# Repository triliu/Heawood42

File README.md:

# Heawood42

The Heawood42 is a diodeless 42-key ortho-linear split keyboard that uses any pro micro microcontroller. The Heawood42 utilises a new type of circuit design stemming from graph theory and mathematical design theory. All previous diodeless keyboards work using one pin per key, such as the [sweep](https://github.com/davidphilipbarr/Sweep), which uses 17 pins to control 17 keys per side, the [sweeeeep](https://fingerpunch.xyz/product/sweeeeep/), which uses 17 pins to control 17 keys per side, the [cantor](https://github.com/diepala/cantor), which uses 18 pins to control 18 keys per side, and the [piantor](https://github.com/beekeeb/piantor), which uses 21 pins to control 21 keys per side. The first two keyboards can use any pro micro-style board (traditionally, the pro micro-style boards have 18 pins available, but one of these pins is required for communication among the halves). The third and fourth keyboard requires the use of a larger microcontroller, the BlackPills and the Raspberry Pi Pico, respectively. 

The Heawood42 is the first split diodeless keyboard requiring fewer pins than keys. Each side uses 14 pins to control 21 keys. This means that even on a typical pro micro-style board, the Heawood42 may have inter-board communication, addressable RGB lights, and an OLED screen. 

Due to its diodeless-ness, the Heawood42 is ideal in several cases, as it reduces the cost and complexity of making a custom mechanical keyboard.

## Why 'Heawood'?

Typical mechanical keyboards arrange their keys in a grid pattern. In such a grid, there are cycles of four keys. If no diodes were used and three keys of a four-key cycle were pressed, the keyboard would act like all four keys were being pressed. See https://pcbheaven.com/wikipages/How_Key_Matrices_Works/ for an explainer of this phenomenon. By adding a diode to every key, the keyboard becomes "n-key rollover", meaning that the keyboard can theoretically distinguish all combinations of keypresses. In software, however, 6-key rollover is typically used, meaning the software assumes that if more than six keys are being pressed, then keys were pressed on accident. The USB keyboard protocol is limited to a 6-key rollover. For split keyboards, a 6-key rollover on each half is excessive, as typically one finger would only press one key at a time, and even a 5-key rollover is more than is needed. 

In graph theory, it is possible to make graphs that do not contain small cycles. Each graph can be converted into a new type of key matrix, with differing characteristics. The Heawood graph is a graph that is the incidence graph of a projective plane of order 2, and has 14 vertices, 21 edges, and a girth of 6. For more details on this graph, see [House of Graphs](https://houseofgraphs.org/graphs/1154). This graph converts to a key matrix with just a 4-key rollover. However, by designing the board specifically, all problematic 5-key and 6-key sequences may be practically eliminated, yielding the Heawood42. 

This design is powered using any pro micro-style microcontroller.

## Versions
- Regular MX-hotswap version
    - 19.05 x 19.05 spacing
    - MX hot-swap style holes (requires 42 MX hot-swap sockets)
    - Per-key RGB LEDs (optional)
- Choc-hotswap version
    - 18 x 17 spacing
    - Choc hot-swap style holes (requires 42 choc hot-swap sockets)
    - Per-key RGB LEDs (optional)

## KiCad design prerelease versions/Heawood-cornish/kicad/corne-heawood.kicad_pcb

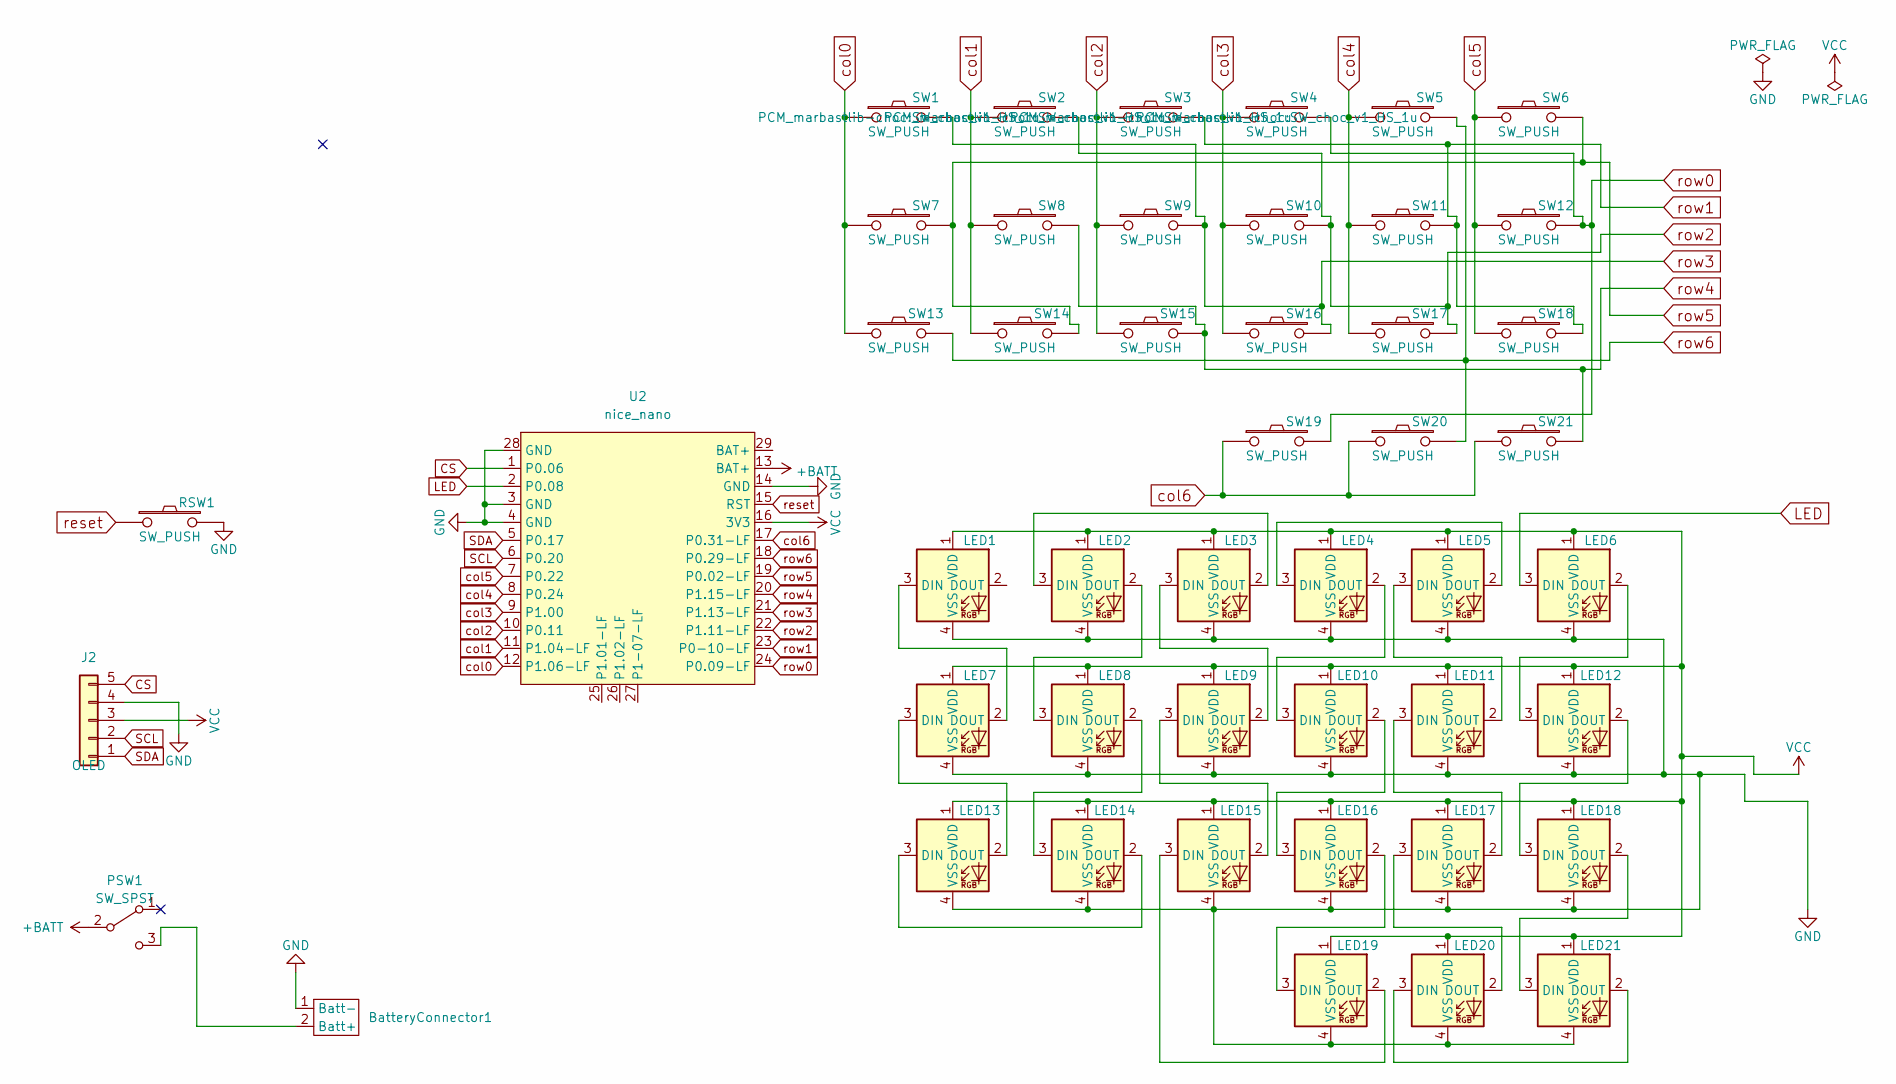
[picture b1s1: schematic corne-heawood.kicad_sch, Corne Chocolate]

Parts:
BatteryConnector1: 2pad_battery_input
J2: OLED; nice_view_1side
LED1, LED2, LED3, LED4, LED5, LED6, LED7, LED8, LED9, LED10, LED11, LED12, LED13, LED14, LED15, LED16, LED17, LED18, LED19, LED20, LED21: SK6812MINI-E; LED_6028R
PSW1: SW_SPST; SW_SPDT_PCM12
RSW1: SW_PUSH; ResetSW
SW1, SW2, SW3, SW4, SW5, SW6, SW7, SW8, SW9, SW10, SW11, SW12, SW13, SW14, SW15, SW16, SW17, SW18, SW19, SW20: SW_PUSH; SW_choc_v1_HS_1u
SW21: SW_PUSH; SW_choc_v1_HS_1.5u
U2: nice_nano; ProMicro_USBdn

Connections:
+BATT: PSW1.2 (B), U2.13 (BAT+)
CS: U2.1 (P0.06); also elsewhere on the board
GND: BatteryConnector1.1 (Batt-), LED1.4 (VSS), LED2.4 (VSS), LED3.4 (VSS), LED4.4 (VSS), LED5.4 (VSS), LED6.4 (VSS), LED7.4 (VSS), LED8.4 (VSS), LED9.4 (VSS), LED10.4 (VSS), LED11.4 (VSS), LED12.4 (VSS), LED13.4 (VSS), LED14.4 (VSS), LED15.4 (VSS), LED16.4 (VSS), LED17.4 (VSS), LED18.4 (VSS), LED19.4 (VSS), LED20.4 (VSS), LED21.4 (VSS), RSW1.2, U2.3 (GND), U2.4 (GND), U2.14 (GND), U2.28 (GND); also elsewhere on the board
LED: LED6.3 (DIN), U2.2 (P0.08)
unnamed 4: BatteryConnector1.2 (Batt+), PSW1.3 (C); also elsewhere on the board
unnamed: LED1.3 (DIN), LED7.2 (DOUT)
unnamed: LED2.3 (DIN), LED3.2 (DOUT)
unnamed: LED2.2 (DOUT), LED8.3 (DIN)
unnamed: LED3.3 (DIN), LED9.2 (DOUT)
unnamed: LED4.3 (DIN), LED5.2 (DOUT)
unnamed: LED4.2 (DOUT), LED10.3 (DIN)
unnamed: LED10.2 (DOUT), LED16.3 (DIN)
unnamed: LED11.3 (DIN), LED17.2 (DOUT)
unnamed: LED5.3 (DIN), LED11.2 (DOUT)
unnamed: LED6.2 (DOUT), LED12.3 (DIN)
unnamed: LED12.2 (DOUT), LED18.3 (DIN)
unnamed: LED13.3 (DIN), LED14.2 (DOUT)
unnamed: LED7.3 (DIN), LED13.2 (DOUT)
unnamed: LED8.2 (DOUT), LED14.3 (DIN)
unnamed: LED15.3 (DIN), LED19.2 (DOUT)
unnamed: LED9.3 (DIN), LED15.2 (DOUT)
unnamed: LED16.2 (DOUT), LED19.3 (DIN)
unnamed: LED17.3 (DIN), LED20.2 (DOUT)
unnamed: LED18.2 (DOUT), LED21.3 (DIN)
unnamed: LED20.3 (DIN), LED21.2 (DOUT)
SCL: U2.6 (P0.20); also elsewhere on the board
SDA: U2.5 (P0.17); also elsewhere on the board
VCC: LED1.1 (VDD), LED2.1 (VDD), LED3.1 (VDD), LED4.1 (VDD), LED5.1 (VDD), LED6.1 (VDD), LED7.1 (VDD), LED8.1 (VDD), LED9.1 (VDD), LED10.1 (VDD), LED11.1 (VDD), LED12.1 (VDD), LED13.1 (VDD), LED14.1 (VDD), LED15.1 (VDD), LED16.1 (VDD), LED17.1 (VDD), LED18.1 (VDD), LED19.1 (VDD), LED20.1 (VDD), LED21.1 (VDD), U2.16 (3V3); also elsewhere on the board
col0: SW1.1, SW7.1, SW13.1, U2.12 (P1.06-LF)
col1: SW2.1, SW8.1, SW14.1, U2.11 (P1.04-LF)
col2: SW3.1, SW9.1, SW15.1, U2.10 (P0.11)
col3: SW4.1, SW10.1, SW16.1, U2.9 (P1.00)
col4: SW5.1, SW11.1, SW17.1, U2.8 (P0.24)
col5: SW6.1, SW12.1, SW18.1, U2.7 (P0.22)
col6: SW19.1, SW20.1, SW21.1, U2.17 (P0.31-LF)
reset: RSW1.1, U2.15 (RST)
row0: SW4.2, SW12.2, SW19.2, U2.24 (P0.09-LF)
row1: SW3.2, SW11.2, SW18.2, U2.23 (P0-10-LF)
row2: SW2.2, SW10.2, SW17.2, U2.22 (P1.11-LF)
row3: SW1.2, SW9.2, SW16.2, U2.21 (P1.13-LF)
row4: SW8.2, SW15.2, SW21.2, U2.20 (P1.15-LF)
row5: SW6.2, SW7.2, SW14.2, U2.19 (P0.02-LF)
row6: SW5.2, SW13.2, SW20.2, U2.18 (P0.29-LF)

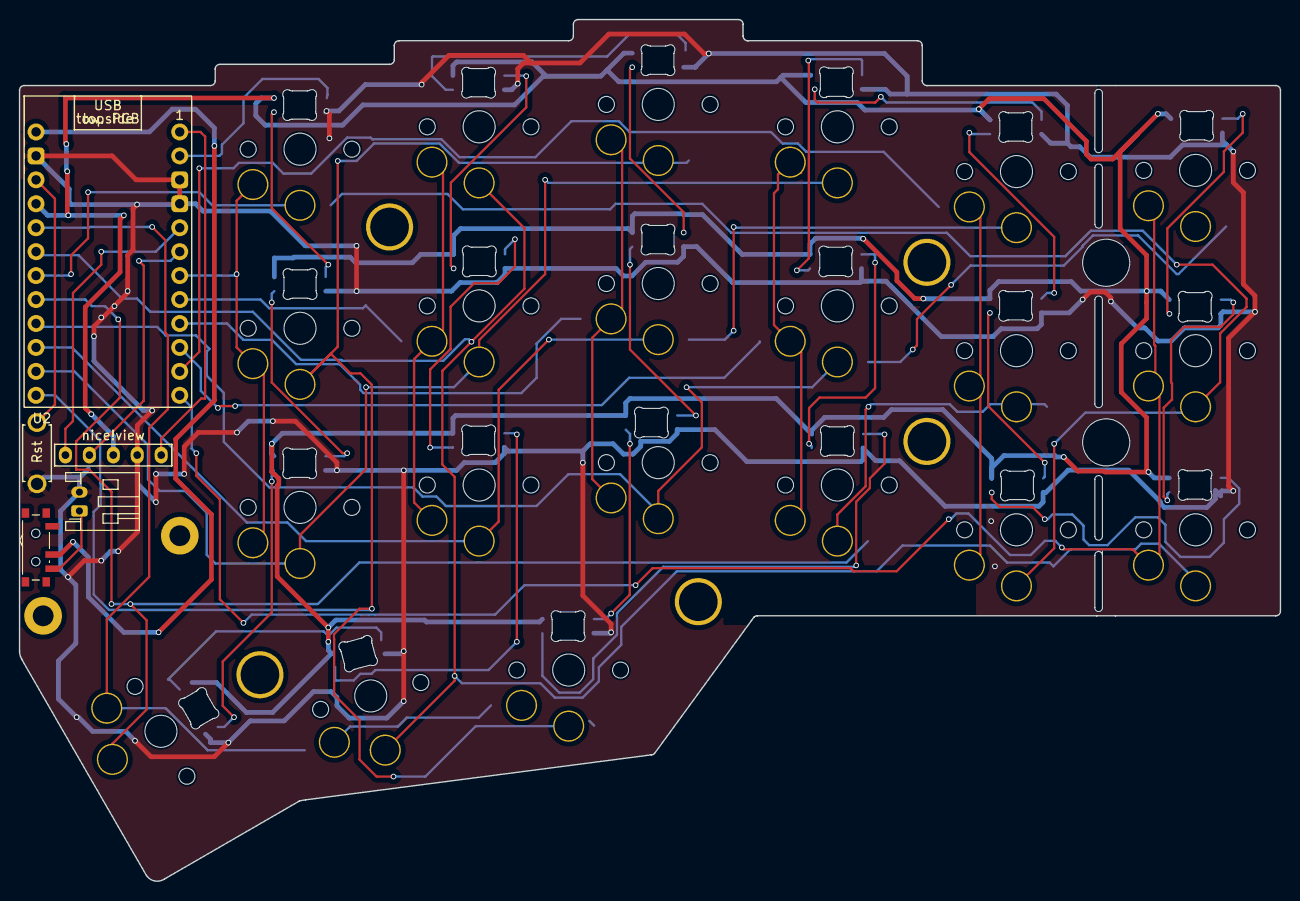
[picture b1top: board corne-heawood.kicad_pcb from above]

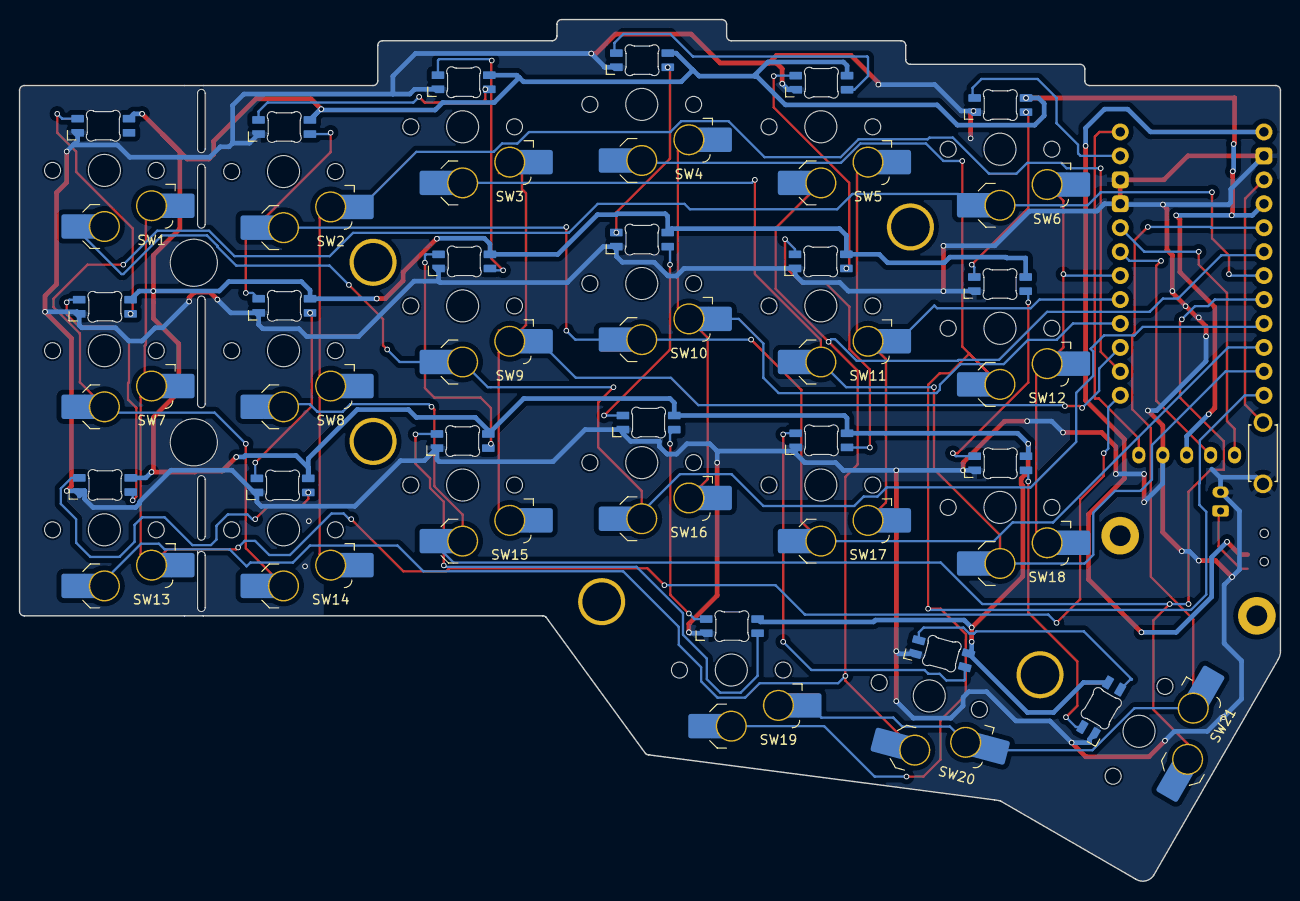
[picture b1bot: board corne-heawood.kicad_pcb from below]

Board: 2 copper layers, 133.8 x 91.4 mm, 47 parts (43 on the bottom side), 43 nets.

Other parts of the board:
BATJ2: Conn_01x02_Female; JST_PH_S2B-PH-K_1x02_P2.00mm_Horizontal
J1: OLED; nice_view_1side

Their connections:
CS: J1.5; also elsewhere on the board
GND: BATJ2.2, J1.4; also elsewhere on the board
unnamed 4: BATJ2.1; also elsewhere on the board
SCL: J1.2; also elsewhere on the board
SDA: J1.1; also elsewhere on the board
VCC: J1.3; also elsewhere on the board

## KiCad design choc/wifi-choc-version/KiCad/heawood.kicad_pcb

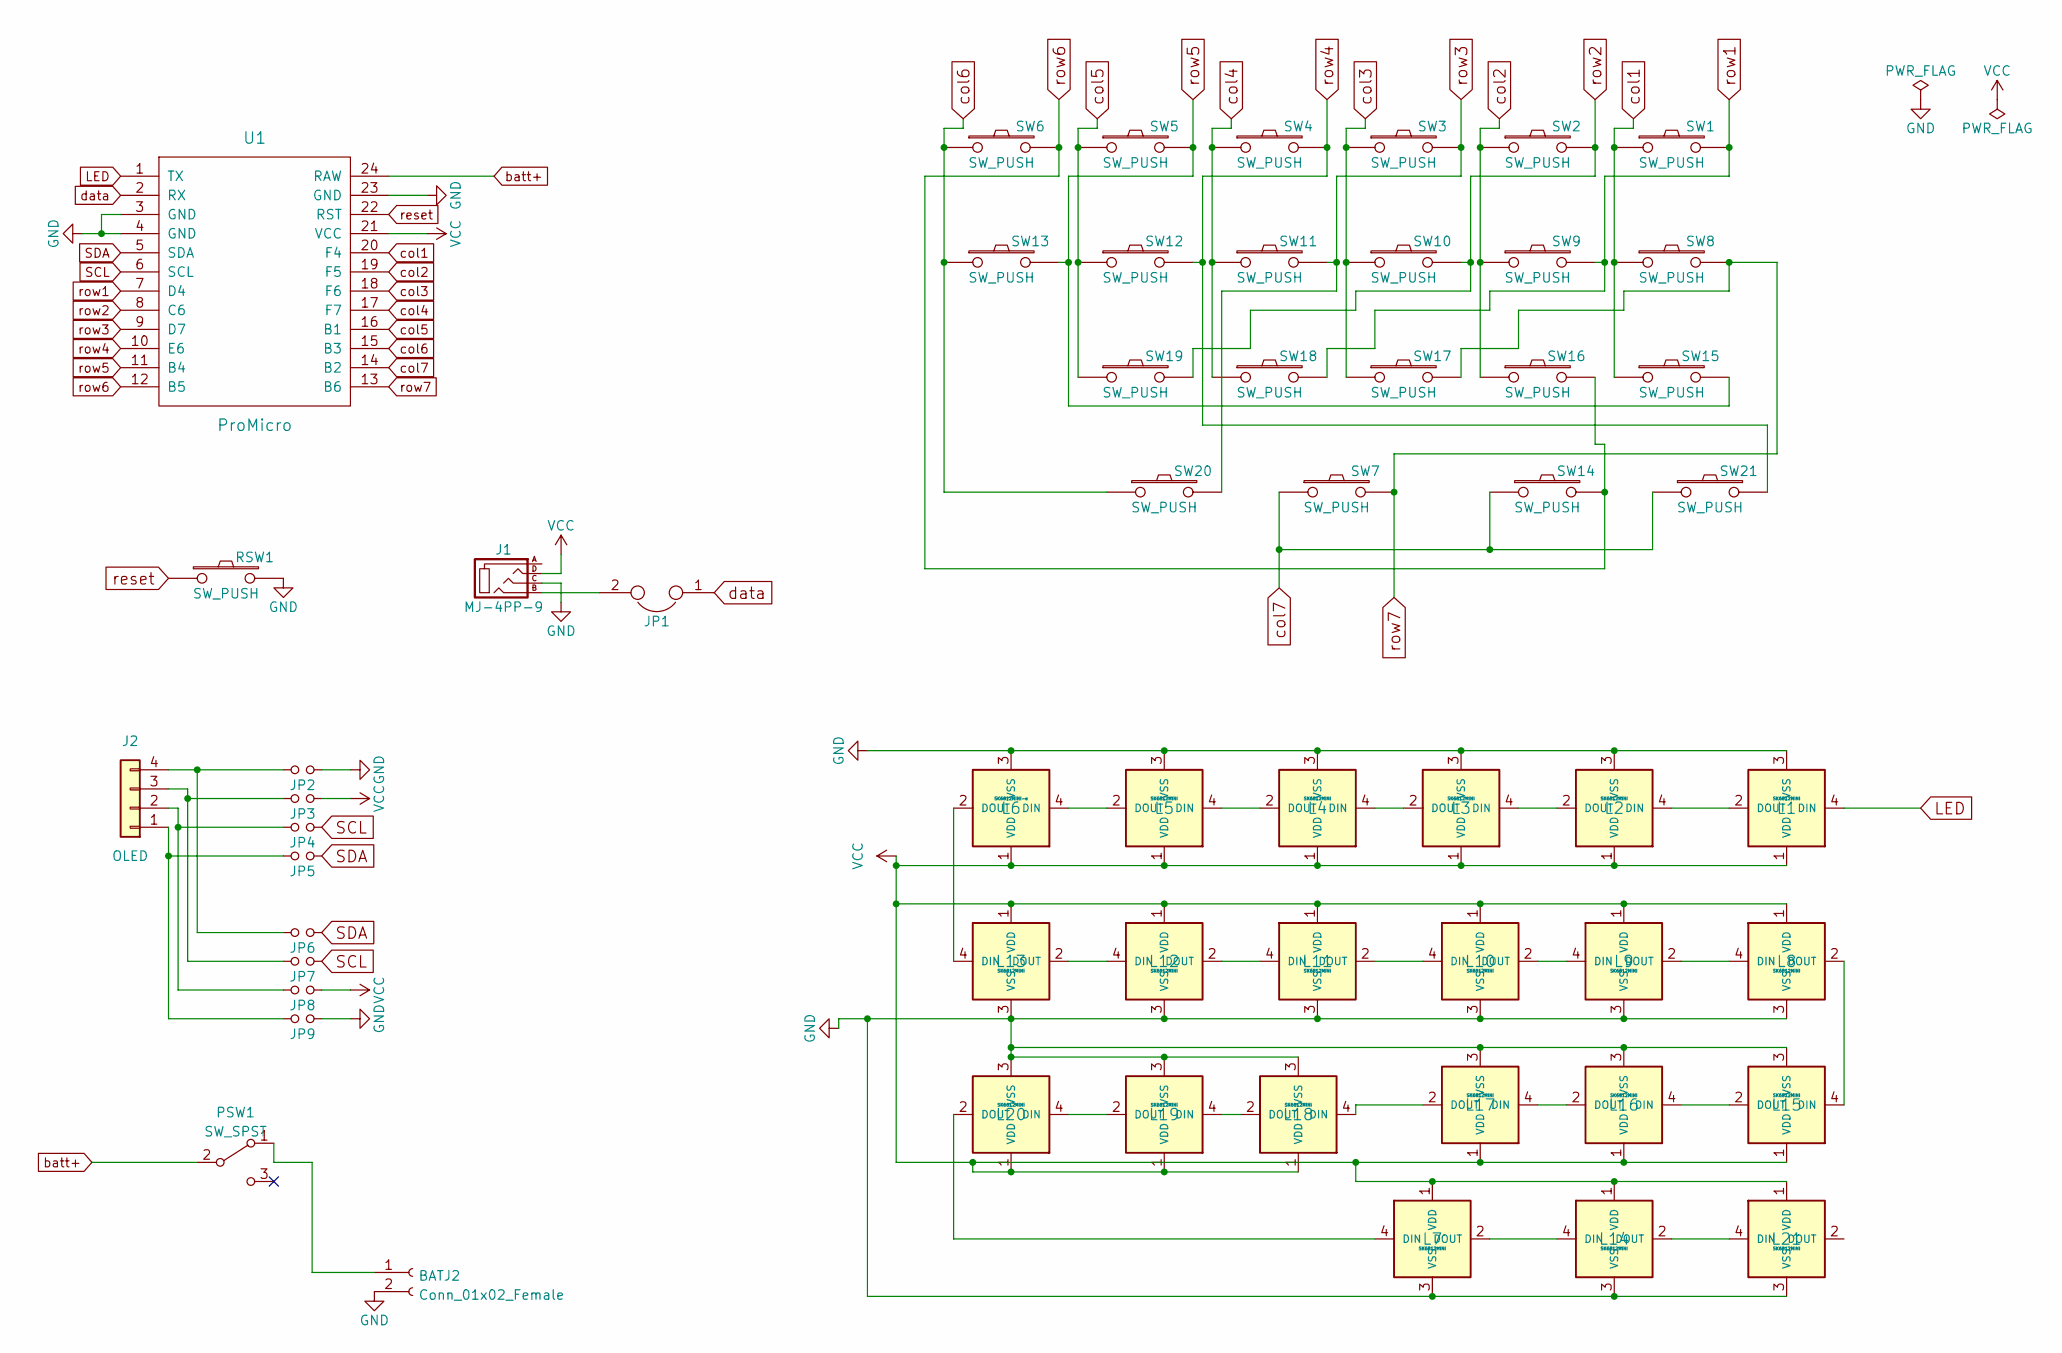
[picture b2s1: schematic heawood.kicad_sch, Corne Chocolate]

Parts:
BATJ2: Conn_01x02_Female; JST_PH_S2B-PH-K_1x02_P2.00mm_Horizontal
J1: MJ-4PP-9; CON_MJ-4PP-9
J2: OLED
JP1: JPC2
JP2, JP3, JP4, JP5, JP6, JP7, JP8, JP9: Jumper
L1, L2, L3, L4, L5, L7, L8, L9, L10, L11, L12, L13, L14, L15, L16, L17, L18, L19, L20, L21: SK6812MINI; YS-SK6812MINI-E
L6: SK6812MINI-e; YS-SK6812MINI-E
PSW1: SW_SPST; SW_SPDT_PCM12
RSW1: SW_PUSH; ResetSW
SW1, SW2, SW3, SW4, SW5, SW6, SW7, SW8, SW9, SW10, SW11, SW12, SW13, SW15, SW16, SW17, SW18, SW19, SW20, SW21: SW_PUSH; Choc_Hotswap
SW14: SW_PUSH; Choc_Hotswap_1.5u
U1: ProMicro; ProMicro_v2

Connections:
GND: BATJ2.2, J1.C, J2.C, JP2.1, JP9.1, L1.3 (VSS), L2.3 (VSS), L3.3 (VSS), L4.3 (VSS), L5.3 (VSS), L6.3 (VSS), L7.3 (VSS), L8.3 (VSS), L9.3 (VSS), L10.3 (VSS), L11.3 (VSS), L12.3 (VSS), L13.3 (VSS), L14.3 (VSS), L15.3 (VSS), L16.3 (VSS), L17.3 (VSS), L18.3 (VSS), L19.3 (VSS), L20.3 (VSS), L21.3 (VSS), RSW1.2, U1.3 (GND), U1.4 (GND), U1.23 (GND); also elsewhere on the board
LED: L1.4 (DIN), U1.1 (TX); also elsewhere on the board
unnamed: BATJ2.1, PSW1.1 (A)
unnamed: J2.1, JP5.2, JP9.2
unnamed: J2.2, JP4.2, JP8.2
unnamed: J2.3, JP3.2, JP7.2
unnamed: J2.4, JP2.2, JP6.2
unnamed: L1.2 (DOUT), L2.4 (DIN)
unnamed: L2.2 (DOUT), L3.4 (DIN)
unnamed: L3.2 (DOUT), L4.4 (DIN)
unnamed: L4.2 (DOUT), L5.4 (DIN)
unnamed: L5.2 (DOUT), L6.4 (DIN)
unnamed: L8.4 (DIN), L9.2 (DOUT)
unnamed: L10.4 (DIN), L11.2 (DOUT)
unnamed: L9.4 (DIN), L10.2 (DOUT)
unnamed: L11.4 (DIN), L12.2 (DOUT)
unnamed: L12.4 (DIN), L13.2 (DOUT)
unnamed: L6.2 (DOUT), L13.4 (DIN)
unnamed: L7.2 (DOUT), L14.4 (DIN)
unnamed: L14.2 (DOUT), L21.4 (DIN)
unnamed: L8.2 (DOUT), L15.4 (DIN)
unnamed: L15.2 (DOUT), L16.4 (DIN)
unnamed: L16.2 (DOUT), L17.4 (DIN)
unnamed: L17.2 (DOUT), L18.4 (DIN)
unnamed: L18.2 (DOUT), L19.4 (DIN)
unnamed: L19.2 (DOUT), L20.4 (DIN)
unnamed: L7.4 (DIN), L20.2 (DOUT)
unnamed 27: J1.A; also elsewhere on the board
unnamed 28: J1.B, JP1.2; also elsewhere on the board
unnamed: PSW1.2 (B), U1.24 (RAW)
SCL: JP4.1, JP7.1, U1.6 (SCL); also elsewhere on the board
SDA: JP5.1, JP6.1, U1.5 (SDA); also elsewhere on the board
VCC: J1.D, JP3.1, JP8.1, L1.1 (VDD), L2.1 (VDD), L3.1 (VDD), L4.1 (VDD), L5.1 (VDD), L6.1 (VDD), L7.1 (VDD), L8.1 (VDD), L9.1 (VDD), L10.1 (VDD), L11.1 (VDD), L12.1 (VDD), L13.1 (VDD), L14.1 (VDD), L15.1 (VDD), L16.1 (VDD), L17.1 (VDD), L18.1 (VDD), L19.1 (VDD), L20.1 (VDD), L21.1 (VDD), U1.21 (VCC); also elsewhere on the board
col1: SW1.1, SW8.1, SW15.1, U1.20 (F4)
col2: SW2.1, SW9.1, SW16.1, U1.19 (F5)
col3: SW3.1, SW10.1, SW17.1, U1.18 (F6)
col4: SW4.1, SW11.1, SW18.1, U1.17 (F7)
col5: SW5.1, SW12.1, SW19.1, U1.16 (B1)
col6: SW6.1, SW13.1, SW20.1, U1.15 (B3)
col7: SW7.1, SW14.1, SW21.1, U1.14 (B2)
data: JP1.1, U1.2 (RX)
reset: RSW1.1, U1.22 (RST)
row1: SW1.2, SW9.2, SW18.2, U1.7 (D4)
row2: SW2.2, SW10.2, SW19.2, U1.8 (C6)
row3: SW3.2, SW11.2, SW20.2, U1.9 (D7)
row4: SW4.2, SW12.2, SW21.2, U1.10 (E6)
row5: SW5.2, SW13.2, SW15.2, U1.11 (B4)
row6: SW6.2, SW14.2, SW16.2, U1.12 (B5)
row7: SW7.2, SW8.2, SW17.2, U1.13 (B6)

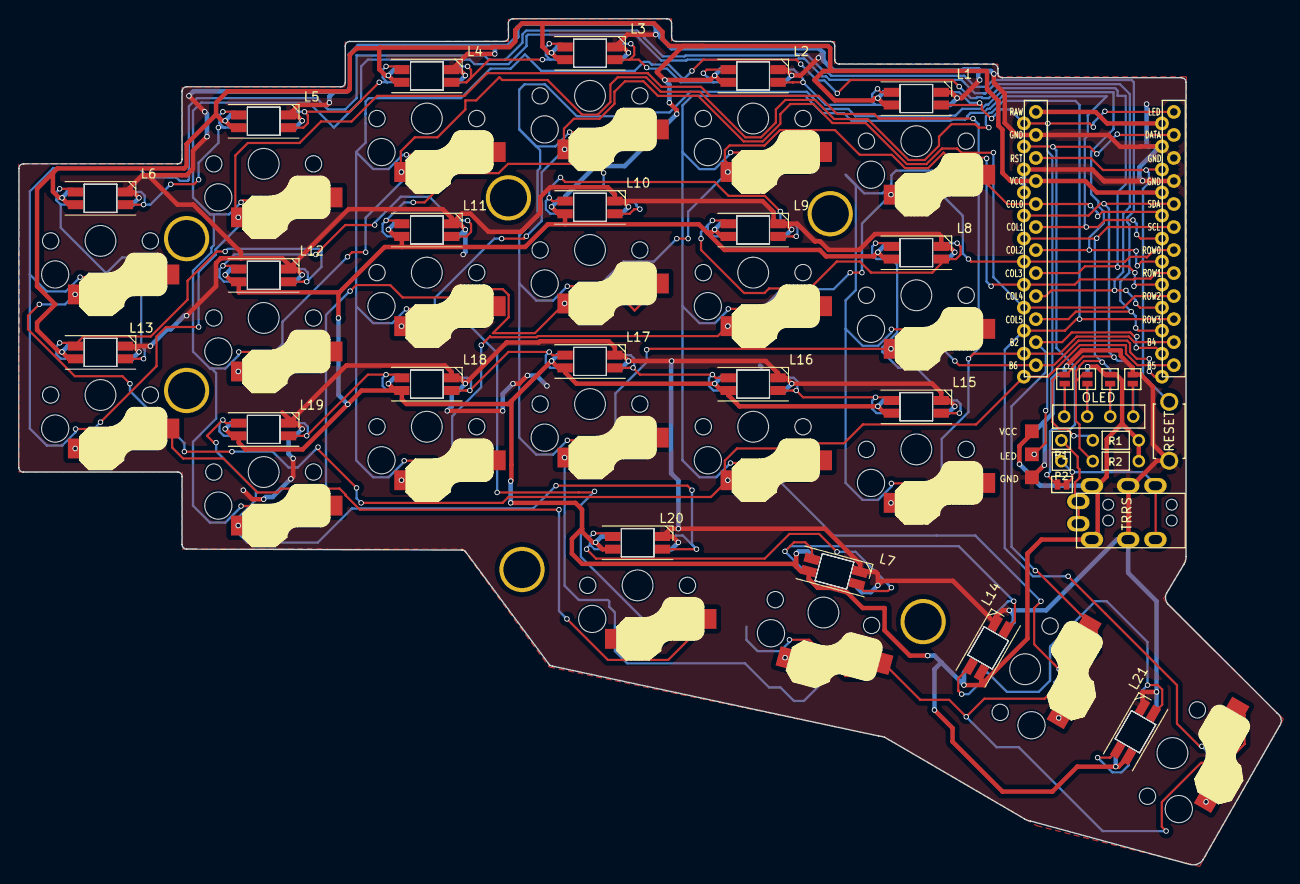
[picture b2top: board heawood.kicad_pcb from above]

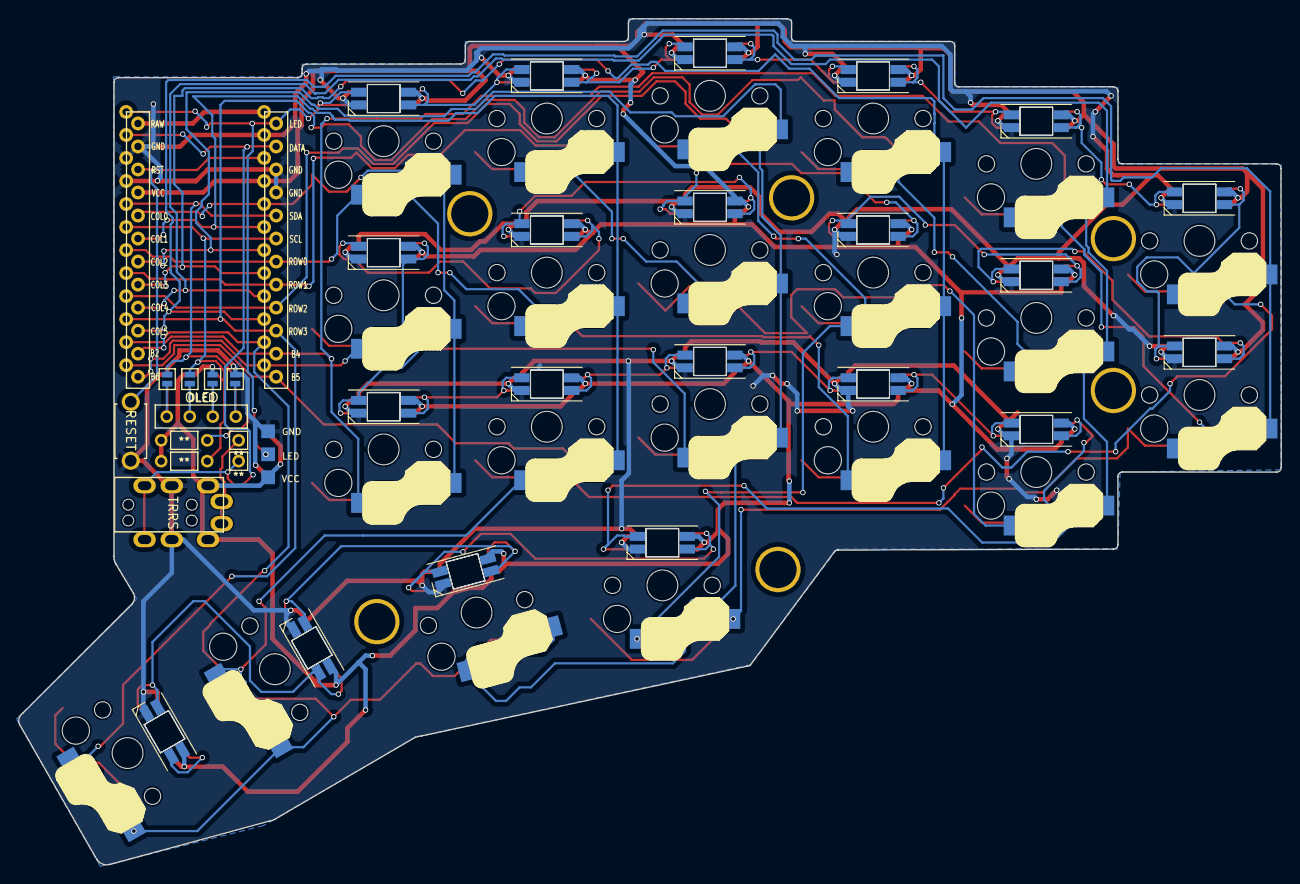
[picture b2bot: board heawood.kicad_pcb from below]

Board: 2 copper layers, 139.3 x 93.3 mm, 60 parts (4 on the bottom side), 47 nets.

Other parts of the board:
J3: LED; StripLED_rev
P1, P2: i2c-pin; 1pin_conn
R1, R2: R

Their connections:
GND: J3.1; also elsewhere on the board
LED: J3.2; also elsewhere on the board
unnamed 27: P1.1; also elsewhere on the board
unnamed 28: P2.1; also elsewhere on the board
SCL: R2.2; also elsewhere on the board
SDA: R1.2; also elsewhere on the board
VCC: J3.3, R1.1, R2.1; also elsewhere on the board

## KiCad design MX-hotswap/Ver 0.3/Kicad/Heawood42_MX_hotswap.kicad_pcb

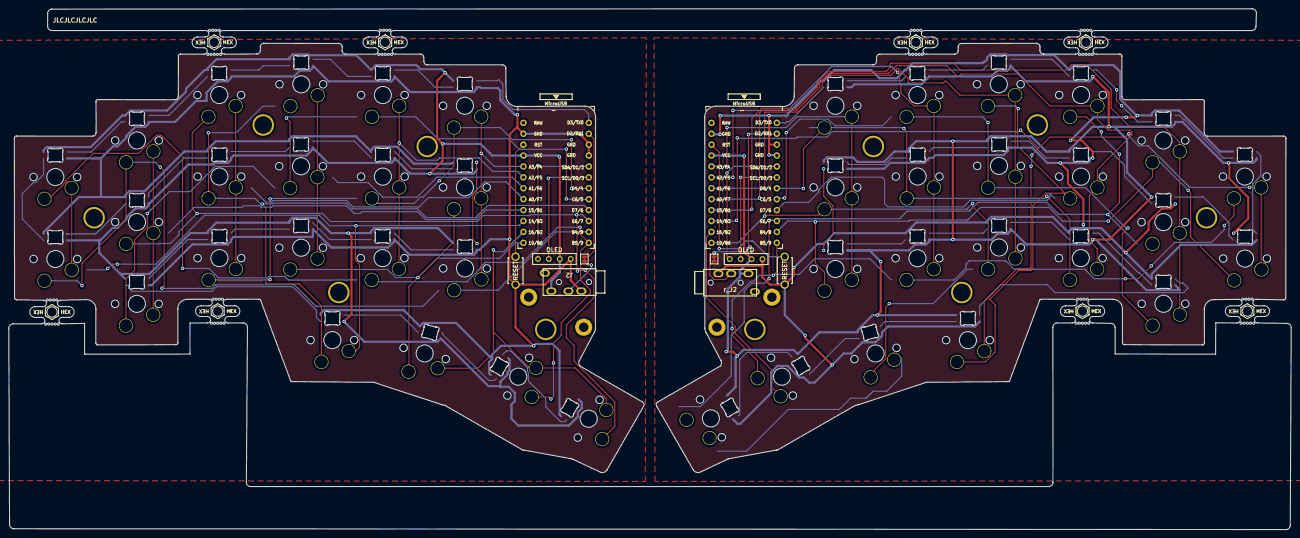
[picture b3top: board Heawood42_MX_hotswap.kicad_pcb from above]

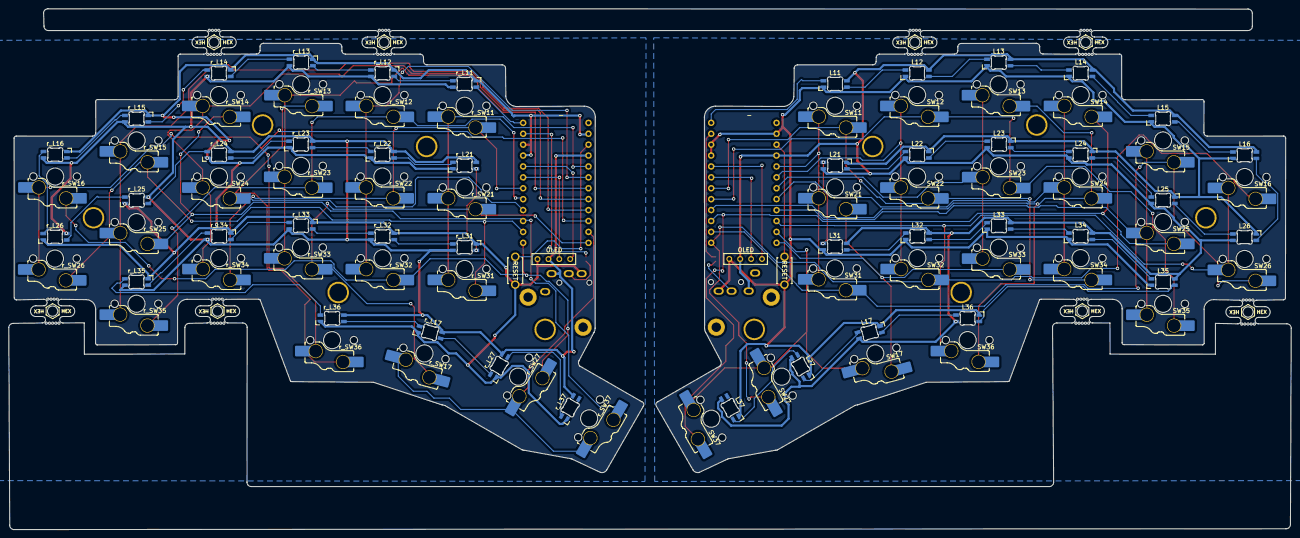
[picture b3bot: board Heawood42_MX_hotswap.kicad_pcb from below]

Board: 2 copper layers, 298.6 x 121.2 mm, 102 parts (85 on the bottom side), 82 nets.

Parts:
J1: OLED
J2: MJ-4PP-9; CON_MJ-4PP-9
JP1: JPC2
L11, L12, L13, L14, L15, L31, L32, L33, L34, L35: SK6812MINI; LED_MX_6812miniE_rev
L16: SK6812MINI-e; LED_MX_6812miniE_rev
L17, L21, L22, L23, L24, L25, L26, L27, L36, L37: SK6812MINI; LED_MX_6812miniE
MB5, MB5#2, MB5#3, MB5#4, MB5#5, MB5#6, MB5#7, MB5#8: 5.5mm; mousebites_5p5mm_easysnap
RSW1: SW_PUSH; ResetSW
SW11, SW12, SW13, SW14, SW15, SW16, SW17, SW21, SW22, SW23, SW24, SW25, SW26, SW31, SW32, SW33, SW34, SW35, SW36, SW37: SW_PUSH; SW_MX_HS_KS-2P02B01-01_1u
SW27: SW_PUSH; SW_MX_HS_KS-2P02B01-01_1.5u
U1: ProMicro; ProMicro_v3.5
r_J1: r_OLED; OLED
r_J2: MJ-4PP-9; CON_MJ-4PP-9
r_JP1: JPC2
r_L11: SK6812MINI-e; LED_MX_6812miniE
r_L12, r_L13, r_L14, r_L15, r_L16, r_L31, r_L32, r_L33, r_L34, r_L35: SK6812MINI; LED_MX_6812miniE
r_L17, r_L21, r_L22, r_L23, r_L24, r_L25, r_L26, r_L27, r_L36, r_L37: SK6812MINI; LED_MX_6812miniE_rev
r_RSW1: SW_PUSH; ResetSW
r_SW11, r_SW12, r_SW13, r_SW14, r_SW15, r_SW16, r_SW17, r_SW21, r_SW22, r_SW23, r_SW24, r_SW25, r_SW26, r_SW31, r_SW32, r_SW33, r_SW34, r_SW35, r_SW36, r_SW37: SW_PUSH; SW_MX_HS_KS-2P02B01-01_1u
r_SW27: SW_PUSH; SW_MX_HS_KS-2P02B01-01_1.5u
r_U1: ProMicro; ProMicro_v3.5

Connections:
GND: J1.4, J2.S, L11.3 (VSS), L12.3 (VSS), L13.3 (VSS), L14.3 (VSS), L15.3 (VSS), L16.3 (VSS), L17.3 (VSS), L21.3 (VSS), L22.3 (VSS), L23.3 (VSS), L24.3 (VSS), L25.3 (VSS), L26.3 (VSS), L27.3 (VSS), L31.3 (VSS), L32.3 (VSS), L33.3 (VSS), L34.3 (VSS), L35.3 (VSS), L36.3 (VSS), L37.3 (VSS), RSW1.2, U1.3 (GND), U1.4 (GND), U1.23 (GND), r_J1.4, r_J2.1, r_L11.3 (VSS), r_L12.3 (VSS), r_L13.3 (VSS), r_L14.3 (VSS), r_L15.3 (VSS), r_L16.3 (VSS), r_L17.3 (VSS), r_L21.3 (VSS), r_L22.3 (VSS), r_L23.3 (VSS), r_L24.3 (VSS), r_L25.3 (VSS), r_L26.3 (VSS), r_L27.3 (VSS), r_L31.3 (VSS), r_L32.3 (VSS), r_L33.3 (VSS), r_L34.3 (VSS), r_L35.3 (VSS), r_L36.3 (VSS), r_L37.3 (VSS), r_RSW1.2, r_U1.3 (GND), r_U1.4 (GND), r_U1.23 (GND)
LED: L11.4 (DIN), U1.1 (TX)
unnamed: J2.R2, JP1.2
unnamed: L11.2 (DOUT), L12.4 (DIN)
unnamed: L12.2 (DOUT), L13.4 (DIN)
unnamed: L13.2 (DOUT), L14.4 (DIN)
unnamed: L14.2 (DOUT), L15.4 (DIN)
unnamed: L15.2 (DOUT), L16.4 (DIN)
unnamed: L16.2 (DOUT), L26.4 (DIN)
unnamed: L17.4 (DIN), L36.2 (DOUT)
unnamed: L17.2 (DOUT), L27.4 (DIN)
unnamed: L21.4 (DIN), L22.2 (DOUT)
unnamed: L21.2 (DOUT), L31.4 (DIN)
unnamed: L22.4 (DIN), L23.2 (DOUT)
unnamed: L23.4 (DIN), L24.2 (DOUT)
unnamed: L24.4 (DIN), L25.2 (DOUT)
unnamed: L25.4 (DIN), L26.2 (DOUT)
unnamed: L27.2 (DOUT), L37.4 (DIN)
unnamed: L31.2 (DOUT), L32.4 (DIN)
unnamed: L32.2 (DOUT), L33.4 (DIN)
unnamed: L33.2 (DOUT), L34.4 (DIN)
unnamed: L34.2 (DOUT), L35.4 (DIN)
unnamed: L35.2 (DOUT), L36.4 (DIN)
unnamed: r_J2.2, r_JP1.2
unnamed: r_L11.2 (DOUT), r_L12.4 (DIN)
unnamed: r_L12.2 (DOUT), r_L13.4 (DIN)
unnamed: r_L13.2 (DOUT), r_L14.4 (DIN)
unnamed: r_L14.2 (DOUT), r_L15.4 (DIN)
unnamed: r_L15.2 (DOUT), r_L16.4 (DIN)
unnamed: r_L16.2 (DOUT), r_L26.4 (DIN)
unnamed: r_L17.4 (DIN), r_L36.2 (DOUT)
unnamed: r_L17.2 (DOUT), r_L27.4 (DIN)
unnamed: r_L21.4 (DIN), r_L22.2 (DOUT)
unnamed: r_L21.2 (DOUT), r_L31.4 (DIN)
unnamed: r_L22.4 (DIN), r_L23.2 (DOUT)
unnamed: r_L23.4 (DIN), r_L24.2 (DOUT)
unnamed: r_L24.4 (DIN), r_L25.2 (DOUT)
unnamed: r_L25.4 (DIN), r_L26.2 (DOUT)
unnamed: r_L27.2 (DOUT), r_L37.4 (DIN)
unnamed: r_L31.2 (DOUT), r_L32.4 (DIN)
unnamed: r_L32.2 (DOUT), r_L33.4 (DIN)
unnamed: r_L33.2 (DOUT), r_L34.4 (DIN)
unnamed: r_L34.2 (DOUT), r_L35.4 (DIN)
unnamed: r_L35.2 (DOUT), r_L36.4 (DIN)
SCL: J1.2, U1.6 (SCL)
SDA: J1.1, U1.5 (SDA)
VCC: J1.3, J2.1, L11.1 (VDD), L12.1 (VDD), L13.1 (VDD), L14.1 (VDD), L15.1 (VDD), L16.1 (VDD), L17.1 (VDD), L21.1 (VDD), L22.1 (VDD), L23.1 (VDD), L24.1 (VDD), L25.1 (VDD), L26.1 (VDD), L27.1 (VDD), L31.1 (VDD), L32.1 (VDD), L33.1 (VDD), L34.1 (VDD), L35.1 (VDD), L36.1 (VDD), L37.1 (VDD), U1.21 (VCC), r_J1.3, r_J2.3, r_L11.1 (VDD), r_L12.1 (VDD), r_L13.1 (VDD), r_L14.1 (VDD), r_L15.1 (VDD), r_L16.1 (VDD), r_L17.1 (VDD), r_L21.1 (VDD), r_L22.1 (VDD), r_L23.1 (VDD), r_L24.1 (VDD), r_L25.1 (VDD), r_L26.1 (VDD), r_L27.1 (VDD), r_L31.1 (VDD), r_L32.1 (VDD), r_L33.1 (VDD), r_L34.1 (VDD), r_L35.1 (VDD), r_L36.1 (VDD), r_L37.1 (VDD), r_U1.21 (VCC)
col1: SW11.1, SW21.1, SW31.1, U1.20 (F4)
col2: SW12.1, SW22.1, SW32.1, U1.19 (F5)
col3: SW13.1, SW23.1, SW33.1, U1.18 (F6)
col4: SW14.1, SW24.1, SW34.1, U1.17 (F7)
col5: SW15.1, SW25.1, SW35.1, U1.16 (B1)
col6: SW16.1, SW26.1, SW36.1, U1.15 (B3)
col7: SW17.1, SW27.1, SW37.1, U1.14 (B2)
data: JP1.1, U1.2 (RX)
r_LED: r_L11.4 (DIN), r_U1.1 (TX)
r_SCL: r_J1.2, r_U1.6 (SCL)
r_SDA: r_J1.1, r_U1.5 (SDA)
r_col1: r_SW11.1, r_SW21.1, r_SW31.1, r_U1.20 (F4)
r_col2: r_SW12.1, r_SW22.1, r_SW32.1, r_U1.19 (F5)
r_col3: r_SW13.1, r_SW23.1, r_SW33.1, r_U1.18 (F6)
r_col4: r_SW14.1, r_SW24.1, r_SW34.1, r_U1.17 (F7)
r_col5: r_SW15.1, r_SW25.1, r_SW35.1, r_U1.16 (B1)
r_col6: r_SW16.1, r_SW26.1, r_SW36.1, r_U1.15 (B3)
r_col7: r_SW17.1, r_SW27.1, r_SW37.1, r_U1.14 (B2)
r_data: r_JP1.1, r_U1.2 (RX)
r_reset: r_RSW1.1, r_U1.22 (RST)
r_row1: r_SW11.2, r_SW22.2, r_SW34.2, r_U1.7 (D4)
r_row2: r_SW12.2, r_SW23.2, r_SW35.2, r_U1.8 (C6)
r_row3: r_SW13.2, r_SW24.2, r_SW36.2, r_U1.9 (D7)
r_row4: r_SW14.2, r_SW25.2, r_SW37.2, r_U1.10 (E6)
r_row5: r_SW15.2, r_SW26.2, r_SW31.2, r_U1.11 (B4)
r_row6: r_SW16.2, r_SW27.2, r_SW32.2, r_U1.12 (B5)
r_row7: r_SW17.2, r_SW21.2, r_SW33.2, r_U1.13 (B6)
reset: RSW1.1, U1.22 (RST)
row1: SW11.2, SW22.2, SW34.2, U1.7 (D4)
row2: SW12.2, SW23.2, SW35.2, U1.8 (C6)
row3: SW13.2, SW24.2, SW36.2, U1.9 (D7)
row4: SW14.2, SW25.2, SW37.2, U1.10 (E6)
row5: SW15.2, SW26.2, SW31.2, U1.11 (B4)
row6: SW16.2, SW27.2, SW32.2, U1.12 (B5)
row7: SW17.2, SW21.2, SW33.2, U1.13 (B6)

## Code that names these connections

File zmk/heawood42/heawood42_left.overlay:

#include "heawood42.dtsi"

&kscan0 {
    col-gpios
        = <&pro_micro 21 GPIO_OPEN_SOURCE> // col1 in the schematic
        , <&pro_micro 20 GPIO_OPEN_SOURCE> // col2 in the schematic
        , <&pro_micro 19 GPIO_OPEN_SOURCE> // col3 in the schematic
        , <&pro_micro 18 GPIO_OPEN_SOURCE> // col4 in the schematic
        , <&pro_micro 15 GPIO_OPEN_SOURCE> // col5 in the schematic
        , <&pro_micro 14 GPIO_OPEN_SOURCE> // col6 in the schematic
        , <&pro_micro 16 GPIO_OPEN_SOURCE> // col7 in the schematic
        ;
};

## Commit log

2024-03-16 Add pre-release cornish heawood
2024-03-20 Added Gerbers
2024-03-22 MX and MX-hotswap updates
2024-03-23 adding zmk files
2024-03-23 small updates
2024-04-16 zmk fix. GPIO are now GPIO_OPEN_SOURCE
2024-04-16 Advanced keymap added
2024-05-10 Add QMK firmware files
2025-08-09 update zmk for zmk studio
